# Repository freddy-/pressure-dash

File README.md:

# Oil and Gas Pressure Dash display

Digital gauge to show engine oil temperature, oil pressure and gas pressure

Schematic

Pictures

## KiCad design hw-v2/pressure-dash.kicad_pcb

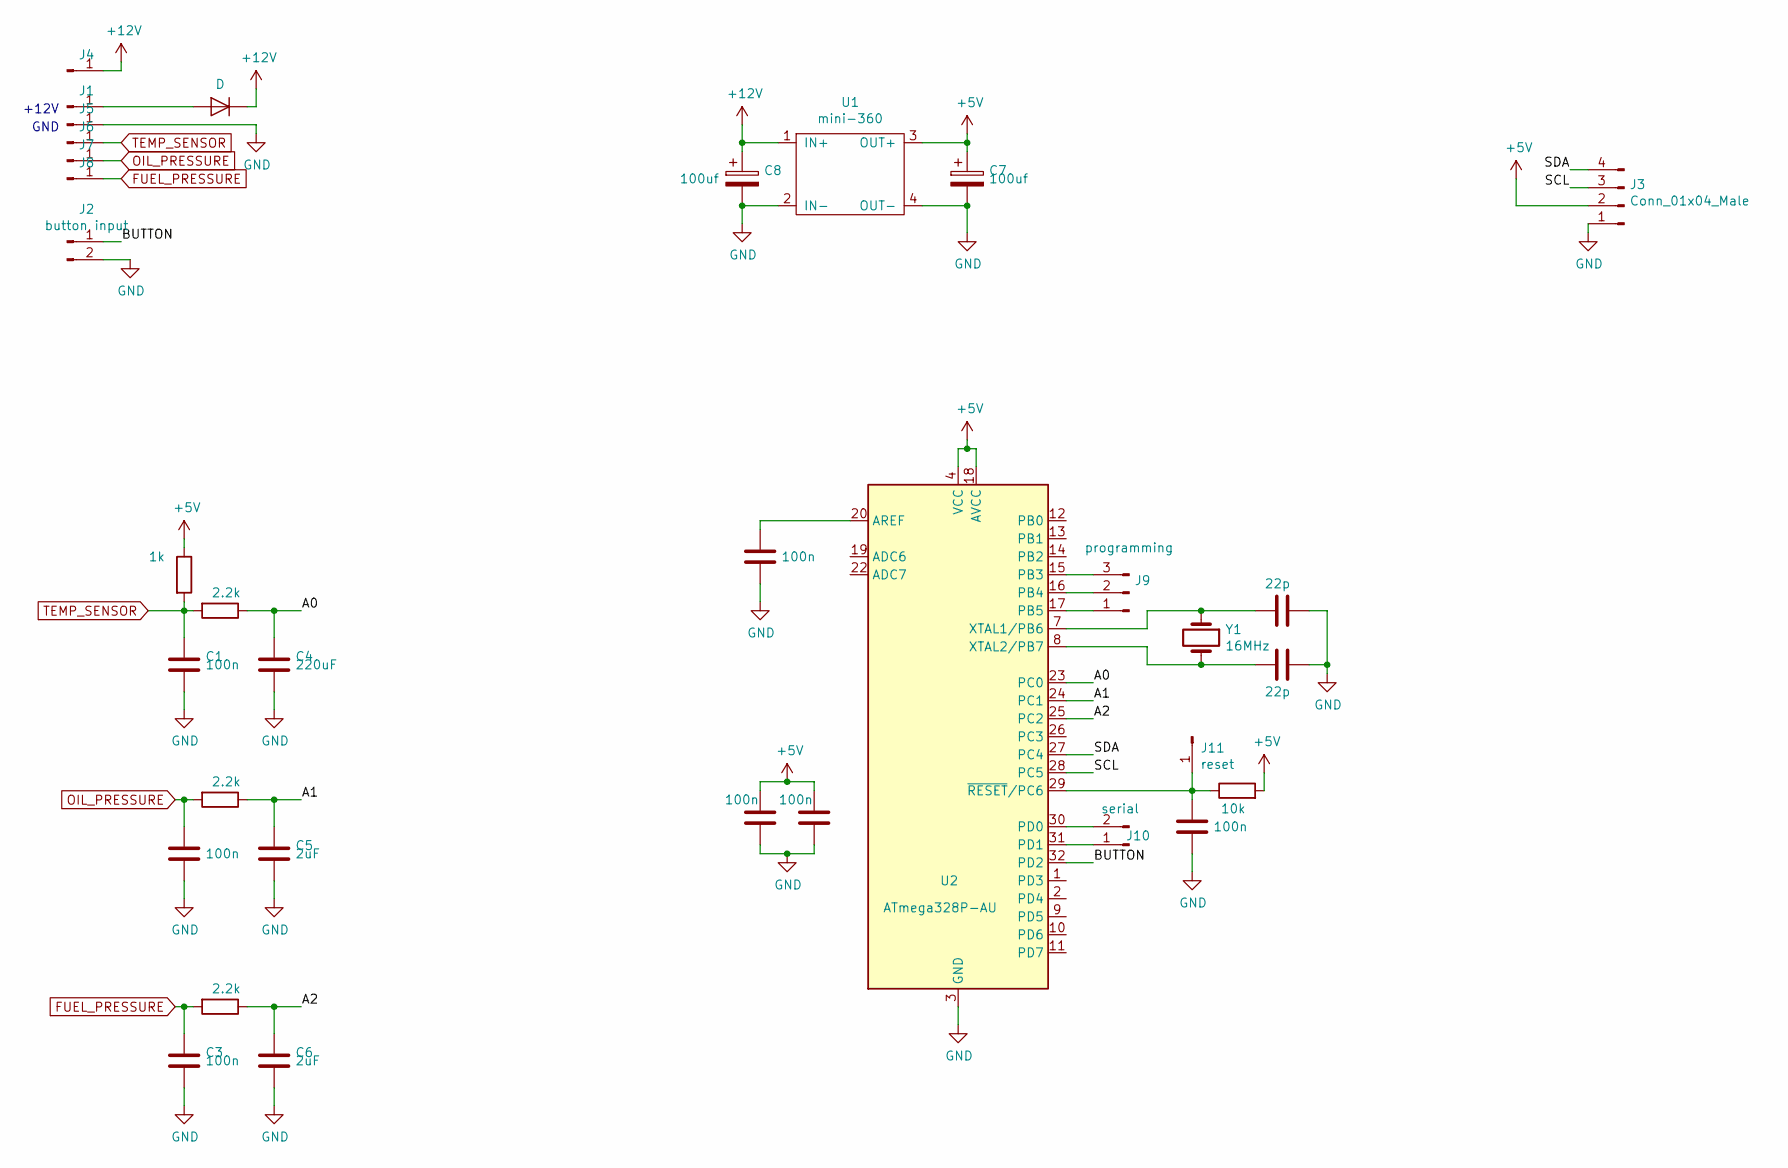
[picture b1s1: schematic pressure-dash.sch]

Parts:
C1, C2, C3, C9, C10, C11, C12: 100n; C_0603_1608Metric_Pad1.05x0.95mm_HandSolder
C4: 220uF; CP_Radial_D5.0mm_P2.50mm
C5, C6: 2uF; C_0805_2012Metric_Pad1.15x1.40mm_HandSolder
C7, C8: 100uf; C_2816_7142Metric_Pad3.20x4.45mm_HandSolder
C13, C14: 22p; C_0603_1608Metric_Pad1.05x0.95mm_HandSolder
D1: D; D_SMB
J1, J4, J5, J6, J7, J8: Conn_01x01_Male; SolderWirePad_1x01_Drill1.2mm
J2: button input; PinHeader_1x02_P2.54mm_Vertical
J3: Conn_01x04_Male; PinHeader_1x04_P2.54mm_Vertical
J9: programming; PinHeader_1x03_P2.54mm_Vertical
J10: serial; PinHeader_1x02_P2.54mm_Vertical
J11: reset; PinHeader_1x01_P2.54mm_Vertical
R1: 1k; R_0603_1608Metric_Pad1.05x0.95mm_HandSolder
R2, R3, R4: 2.2k; R_0603_1608Metric_Pad1.05x0.95mm_HandSolder
R5: 10k; R_0603_1608Metric_Pad1.05x0.95mm_HandSolder
U1: mini-360
U2: ATmega328P-AU; TQFP-32_7x7mm_P0.8mm
Y1: 16MHz; Crystal_HC52-U_Vertical

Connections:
+5V: C7.1, C10.1, C11.1, J3.2, R1.1, R5.2, U1.3 (OUT+), U2.4 (VCC), U2.6 (VCC), U2.18 (AVCC)
+12V: C8.1, D1.1 (K), J4.1, U1.1 (IN+)
/A0: C4.1, R2.1, U2.23 (PC0)
/A1: C5.1, R3.1, U2.24 (PC1)
/A2: C6.1, R4.1, U2.25 (PC2)
/BUTTON: J2.1, U2.32 (PD2)
/SCL: J3.3, U2.28 (PC5)
/SDA: J3.4, U2.27 (PC4)
FUEL_PRESSURE: C3.1, J8.1, R4.2
GND: C1.2, C2.2, C3.2, C4.2, C5.2, C6.2, C7.2, C8.2, C9.2, C10.2, C11.2, C12.2, C13.1, C14.1, J2.2, J3.1, J5.1, U1.2 (IN-), U1.4 (OUT-), U2.3 (GND), U2.5 (GND), U2.21 (GND)
unnamed: C9.1, U2.20 (AREF)
unnamed: C12.1, J11.1, R5.1, U2.29 (~RESET~/PC6)
unnamed: C13.2, U2.7 (XTAL1/PB6), Y1.1
unnamed: C14.2, U2.8 (XTAL2/PB7), Y1.2
unnamed: D1.2 (A), J1.1
unnamed: J9.1, U2.17 (PB5)
unnamed: J9.2, U2.16 (PB4)
unnamed: J9.3, U2.15 (PB3)
unnamed: J10.1, U2.31 (PD1)
unnamed: J10.2, U2.30 (PD0)
OIL_PRESSURE: C2.1, J7.1, R3.2
TEMP_SENSOR: C1.1, J6.1, R1.2, R2.2

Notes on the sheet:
+12V
GND

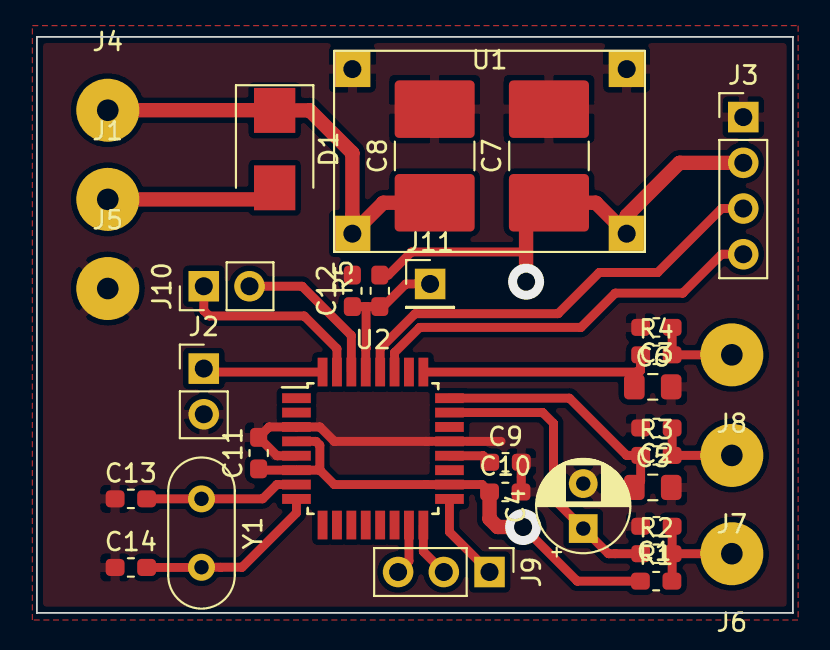
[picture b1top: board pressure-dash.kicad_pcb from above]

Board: 2 copper layers, 42.0 x 32.0 mm, 34 parts (0 on the bottom side), 22 nets.

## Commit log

2020-07-15 Fix readme images
2020-07-17 Create screen for temperature and pressure reading
2020-07-19 Fix schematic and calibration values
2020-07-19 Update schematic image
2020-07-25 Change presure reading to resistance
2020-07-25 Fix function name
2020-08-01 Calibrate pressure sensors
2020-12-07 Change to 3 wire (1v - 5v) pressure sensor
2020-12-07 Add description
2020-12-07 Update schematic
2021-06-03 Refactor for 0-5v pressure sensor
2022-07-02 Use i2c timeout to prevent display freezing
2022-07-02 Create v2 pcb
